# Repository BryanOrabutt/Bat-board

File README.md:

# Bat-board
Ultrasonic 'Lidar' board.
by Bryan Orabutt

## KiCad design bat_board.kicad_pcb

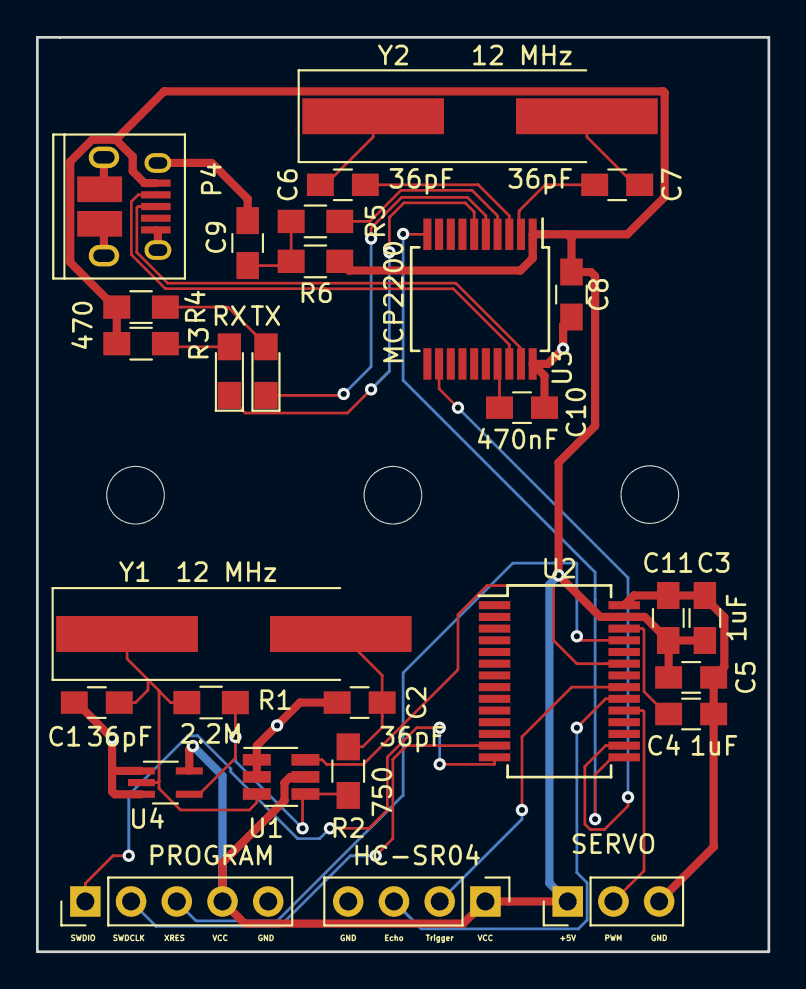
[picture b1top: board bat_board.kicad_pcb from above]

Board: 2 copper layers, 40.6 x 50.8 mm, 29 parts (0 on the bottom side), 28 nets.

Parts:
C1, C2, C6, C7: 36pF; C_0805_HandSoldering
C3, C4: 1uF; C_0805_HandSoldering
C5, C8, C9, C11: 100nF; C_0805_HandSoldering
C10: 470nF; C_0805_HandSoldering
D1: TX; LED_0805_HandSoldering
D2: RX; LED_0805_HandSoldering
P1: PROGRAM; Pin_Header_Straight_1x05_Pitch2.54mm
P2: HC-SR04; Pin_Header_Straight_1x04_Pitch2.54mm
P3: SERVO; Pin_Header_Straight_1x03_Pitch2.54mm
P4: USB_OTG; USB_Micro-B_10103594-0001LF
R1: 2.2M; R_0805_HandSoldering
R2: 750; R_0805_HandSoldering
R3, R4, R5: 470; R_0805_HandSoldering
R6: 10k; R_0805_HandSoldering
U1: SN74LVC1GX04DBVR; SOT-23-6_Handsoldering
U2: CY8C4124PVI-432; SSOP-28_5.3x10.2mm_Pitch0.65mm
U3: MCP2200; SSOP-20_5.3x7.2mm_Pitch0.65mm
U4: SN74LVC1GU04DCKR; SOT-353_SC-70-5_Handsoldering
Y1, Y2: 12 MHz; Crystal_SMD_HC49-SD_HandSoldering

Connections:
+5V: C3.1, C5.1, C8.2, C11.1, P1.4, P2.1, P3.1, P4.1, R3.1, R4.2, R6.1, U1.5, U2.27, U3.1, U4.5
/ECHO: P2.3, U2.20
/PSoC_RX: U2.15, U3.10
/PSoC_TX: U2.16, U3.12
/PWM: P3.2, U2.19
/TRIG: P2.2, U2.21
/XCLK: U1.6, U2.23
/XRES: P1.3, U2.25
GND: C1.1, C2.1, C3.2, C4.1, C5.2, C8.1, C9.1, C10.1, C11.2, P1.5, P2.4, P3.3, P4.5, P4.6, U1.1, U1.2, U2.28, U3.20, U4.1, U4.3
unnamed: C1.2, R1.1, U1.3, U4.2, Y1.1
unnamed: C2.2, R2.1, Y1.2
unnamed: C4.2, U2.26
unnamed: C6.1, U3.3
unnamed: C6.2, Y2.1
unnamed: C7.1, U3.2
unnamed: C7.2, Y2.2
unnamed: C9.2, R5.1, R6.2
unnamed: C10.2, U3.17
unnamed: D1.1, U3.5
unnamed: D1.2, R4.1
unnamed: D2.1, U3.6
unnamed: D2.2, R3.2
unnamed: P1.1, U2.14
unnamed: P1.2, U2.13
unnamed: P4.2, U3.18
unnamed: P4.3, U3.19
unnamed: R1.2, R2.2, U1.4, U4.4
unnamed: R5.2, U3.4

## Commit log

2017-10-06 Test
2017-10-09 Designed schmeatic and board. Needs verification on dimensions
